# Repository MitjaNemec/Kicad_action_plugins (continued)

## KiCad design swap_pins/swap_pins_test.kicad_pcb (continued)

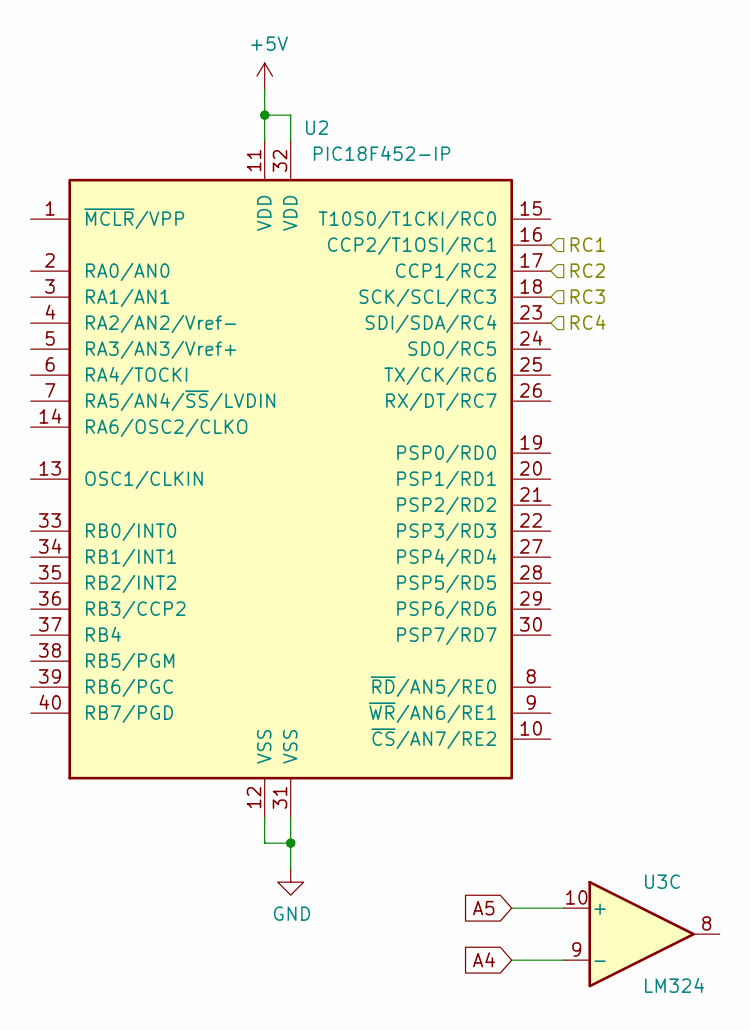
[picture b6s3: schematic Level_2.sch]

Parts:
U1: LM324
U301: PIC18F452-IP; DIP-40_W15.24mm

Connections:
+5V: U301.11 (VDD), U301.32 (VDD); also elsewhere on the board
/level_1/Lavel_2/RC1: U301.16 (CCP2/T1OSI/RC1); also elsewhere on the board
/level_1/Lavel_2/RC2: U301.17 (CCP1/RC2); also elsewhere on the board
/level_1/Lavel_2/RC3: U301.18 (SCK/SCL/RC3); also elsewhere on the board
/level_1/Lavel_2/RC4: U301.23 (SDI/SDA/RC4); also elsewhere on the board
A4: U1.9 (-); also elsewhere on the board
A5: U1.10 (+); also elsewhere on the board
GND: U301.12 (VSS), U301.31 (VSS); also elsewhere on the board

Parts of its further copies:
U2: PIC18F452-IP; DIP-40_W15.24mm

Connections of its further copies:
+5V: U2.11 (VDD), U2.32 (VDD); also elsewhere on the board
/level_1/Level2b/RC1: U2.16 (CCP2/T1OSI/RC1)
/level_1/Level2b/RC2: U2.17 (CCP1/RC2)
/level_1/Level2b/RC3: U2.18 (SCK/SCL/RC3)
/level_1/Level2b/RC4: U2.23 (SDI/SDA/RC4)
GND: U2.12 (VSS), U2.31 (VSS); also elsewhere on the board

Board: 2 copper layers, 24 parts (0 on the bottom side), 23 nets, no tracks yet.

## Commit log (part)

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2018-06-20 Working version
2018-06-20 Add test project file
2018-06-20 changed project to include hierarchical labels also
2018-06-20 Added documentation
2018-06-20 switch to complex plugin type (easier testing)
2018-06-21 Added swap units documentation
2018-06-21 cleanup
2018-06-26 Added instrumentation code to swap_unit
2018-06-27 Fixed an issue when parsing sch files for subsheets
2018-06-27 Minor code formating changes
2018-06-30 Replicate layout: sort replicated sheets.
    Sort sheets to be replicated by the number portion of the reference of
    the pivot module. This means the order is stable (doesn't depend on the
    order the modules are loaded). It also looks better on the PCB as the
    references increment nicely between blocks rather than jumping all over
    the place.
2018-06-30 Replicate layout: copy local module settings.
    The local clearance, solder mask, solder paste margin, solder paste
    margin ratio and zone connection style should be copied to the cloned
    modules.
2018-07-01 Replicate layout: allow text objects to be replicated
    Adds support for replicating standalone text objects (i.e., text not
    associated with a footprint such as a reference). This is a separate
    option in the dialog box (defaults to on) and includes support for
    removing existing text objects from the zones to be cloned.
2018-07-11 Added instrumentation
2018-07-13 Overwritten the plugin with V2 version
2018-08-03 Bugfix to archive-project
    Updated to support spaces in subsheet names. May be OSX specific.
2018-08-17 Updated test files for V5.0
2018-08-17 Changed test project to include complex hierarchy
2018-08-27 adding layout with top level replication done, for bottom level testing
2018-08-28 updated correct test boards
2018-08-29 changed test board for better documentation recording
2018-08-30 Updated documentation of replicate_layout
2018-08-30 Added automatic detection of open Eeschema window
2018-09-11 Fixed a bug in swap_unit plugin to support swapping units where only one unit is placed
2018-09-15 Bugfix: archive_project, handle copy of already archived 3D models gracefully
2018-09-24 Replicate all module text settings
2018-10-09 mode test_project in dedicated folder
2018-10-10 Allow multiple invokations of the archive_project plugin
2018-11-02 Improvements to readme
2018-11-08 Fixed a bug getting the wx.frame due to case of pcbnew application name
    Fixes #22
2018-11-13 Changed the GUI layout for ReplicateLayout
2018-11-23 Additional instrumentation
2018-11-28 Fixed a bug, when a line in .sch file starts with L but is not a part of component description (e.g. Labels, Text, ...)
2018-12-04 Fixed instrumentation
2018-12-20 Allow plugin window to be resized
2019-01-22 managed to keep messagebox focused
2019-01-23 Bugfix: Handle invalid selection of pivot module if selected module is on root level of hierarchy
    Fixes #31
2019-01-31 Gracefully handle common pins swapping Fixed an additional bug
2019-01-31 Fixed another bug in swap_pins
2019-02-02 Add additional layer of error reporting to catch and log errors when trying to run the plugin fails
2019-02-02 minor development enhancement
2019-02-02 Partial fix for complex hierarchy replication. Needs further testing
2019-02-03 Added tests to replicate_layout
2019-02-13 cleaned up the test code
2019-02-13 Added a stub for place_footprints action plugin GUI is more or less in place
2019-02-14 Placement by sheet tested
2019-02-15 Started to update the documentation
2019-02-16 Finalized test code
2019-02-17 Fixed circular placement
2019-02-18 Added forgoten file
2019-02-18 Change GUI a bit in order to enable additional placement options
2019-02-20 Corrected info in copy pasted file header
2019-02-20 Added documentation for net2net action plugin
2019-02-26 upadte info on which versions do net2net and pad2pad work
2019-02-26 update documentation
2019-03-02 Add anchor module reference to the sheet list
2019-03-03 Added calculation of resistance,
2019-03-08 Added length stats plugin with documentation
2019-03-12 updated test suite
2019-03-12 refreshed test suite
2019-03-12 minor change in test code
2019-03-16 updated test project
2019-03-16 Tested archive_project on V5.1
2019-03-17 Added icons
2019-03-19 Split GUI code so that it is completely autogenerated by WxFormBuilder
2019-03-19 Split GUI code
2019-03-19 Tidy up the icons
2019-03-20 Allow selecting tracks, vias or pads
    Fixes #34
2019-03-21 Fixed python3 fix
2019-03-21 Improved error message
2019-03-22 Bugfix (typo)
2019-03-25 Refactor relative local imports to enable back running as a script
2019-03-26 Add flush method to StreamToLogger class for python3 compatibility
    https://github.com/locustio/locust/issues/475
2019-03-26 Added initial instrumentation
2019-03-26 Fix crash when connection between pads has not been found
    Fixes #37
2019-03-27 Python3 compatibility fix
2019-03-27 Added instrumentation, minor styling changes
2019-03-28 First attempt at multiple hierarchy fix. Tested on one project
2019-03-28 instrumentation bugfix
2019-03-28 modified test project
2019-03-29 Fixed handling of multiple hierarchy in swap_pins
2019-04-01 Improved error handling for known errors.
2019-04-02 Allow resize of archive_project GUI
2019-04-02 Fix handling sheet names containing spaces
2019-04-02 Allow resizing of dialog windows
2019-04-09 Added internal version numbers with start commit hook
2019-04-09 SImplified text replication
2019-04-10 Improved errormessages, added error handling
2019-04-11 logging and UI naming cleanup (mostly modules->footprints)
    # Conflicts:
    # copy_layout/copy_layout.py
2019-04-12 Fixed an import bug
2019-04-15 Fixed a bug when swapping units on the same page. Introduced in 8af9e287
2019-04-18 added test suite with reference projects. Reference project have to be checked
2019-04-19 updated test projects
2019-04-19 Added test projects
2019-04-19 Modify test project
2019-04-19 initial architecture in place
2019-04-19 Modified test project. Successfule began importing layout
2019-04-19 saving layout works
2019-04-19 refactor classes
2019-04-19 Applied refactoring, change to saving pickled data
2019-04-19 GUI elements, tested in standalone mode Temporary file handling can be improved
2019-04-19 added forgoten files to test project
2019-04-19 Added icon file
2019-04-19 Added instrumentation and exception handling
2019-04-19 changed test project Added gif animation
2019-04-20 refactor pa2pad to generated GUI code
2019-04-20 Fix bug with swapped models always having wrl ext
    ... regardless of what was actually copied over.
2019-04-24 Added and modified instrumentation
2019-04-24 Updated reference test project
2019-04-24 Added a bit of instrumentation
2019-05-06 added support for any footprint to serve as a reference in linear and circular mode
2019-05-10 Added option to remove nets from the list in lenght_stats
2019-05-11 changed idalog to frame. Does not help
2019-05-12 sort list of netnames
2019-05-12 Sorting by column works
2019-05-16 Solved the highlightning issue
2019-05-21 fixed a bug: forgot to change GUI code in previous commit
2019-05-21 Added logging.shutdown to flush the log
2019-06-18 Additional error checking
2019-06-18 Changed standalone logging added instrumentation
2019-07-15 added plugin icon for lenght_stats
2019-07-27 Added highlight feature to place_footprints
2019-07-28 Added highlight feature to replicate_layout
2019-07-28 updated test project with documentation files
2019-07-28 Solved the GUI issue with documentation checkbox
2019-07-29 swap pcbnew.MODULE.PadsList() as it is removed in newer versions of KiCad for pcbnew.MODULE.Pads()
2019-07-29 Possible fix for V6 compatibility bug
2019-07-30 Swap last couple of calls to *List methods
2019-07-30 cleanup after zone replication refactoring
2019-07-30 Refactor track replication
2019-07-31 Refactored track/via restoration
2019-07-31 Added highlight feature
2019-08-21 Bugfix for matrix layout
    Fixes #61
2019-08-24 Minor UI enhancement
2019-09-04 Archiving worksheet
2019-09-04 Archive both worksheets (PCB ans SCH)
2019-09-06 working progress bar, without threading
2019-09-09 Towards progress report
2019-09-11 Partial fix for issue #64
2019-09-11 Fix the not connected zone replication bug
2019-09-12 Toggle the compatibility hack
2019-09-19 progress bar GUI tested, fixed update of message
2019-10-03 changed the initial position of the dialog
2019-10-07 replicate_layout dialog should now be positioned properly even with multiple screen setup
2019-10-09 correction to Assertion "aNetInfo->GetBoard() == GetBoard()" failed.
2019-10-09 logger.info corrected
2019-10-20 Added option to remove duplicate items (tracks, zones, drawings, text)
2019-11-12 Properly handle nonexistent sheet templates
2019-11-17 Additional instrumentation, proper handling of 3Dmodels with nonexistent path
2019-11-20 Change test project
2019-12-20 Fixed a bug when downloading documentation if it was not a .pdf file
2019-12-29 Bugfix for #74
2020-01-10 Fix syntax error.
    Fixes #76
2020-01-25 Fix case sensitive bug
2020-02-03 Replicate "Keep Upright" as well
    This is necessary for (left,right)-justified text that gets rotated on
    replication. The text will flow in the wrong direction otherwise.
2020-02-16 updated test layouts as the zone filling algorithm changed between 5.1.2 and 5.1.5
2020-02-20 replicate_layout: added option to keep locked footprints in their original position
2020-02-24 Update wxformbuilder->updated generated GUI code
2020-02-24 Removed unused parameter
2020-03-01 Removed unneeded code, changed GUI a bit
2020-03-05 Added os and build version info to log file
2020-03-08 Fixed the 5.1x and 5.99 compatibility
2020-03-08 Removed pcbnew python mocking for 5.1x and 5.99 compatibility. Added intermediate methods to solve this
2020-03-10 Additional fixes for 5.00 getpath compatibility
2020-03-14 Fixed a bug when deleting items when iterating through all items
2020-03-28 change module path compatibility method vith jvpap's approach
2020-03-29 Applied Forty-Bot's bugfix to other instances of get_path
2020-03-30 Gui changes to "source", "destination" nomenclature
2020-04-07 minor documentation corrections
2020-04-11 Add warning for 5.99 users.
2020-06-14 Additional checking for proper schematics and emiting a proper error message
2020-06-14 Place selected footprints only
2020-06-24 Read schematic files as UTF-8
    This allows for UTF-8 in schematic files. As ASCII is also valid UTF-8,
    this is a non-breaking change.
2020-06-25 Added 2.7 compatibility with open file utf-8 support
2020-07-09 fixed a bug when parsing version (introduced when reading files as utf8)
2020-07-22 IndentFixes
2020-08-03 place by selection implemented
2020-12-16 Removed instrumentation
2021-01-07 Better Git Integration
    Added __init__.py so that the plugins can be included in other git projects as a submodule.
2021-01-25 Add sexp_parser
2021-02-03 update README.md with info on 5.99 branch
2021-02-05 Further 5.99 bugfixes
2021-02-19 Updated length_stats/LenghtStats_GUI.fbp Added sorting to the length_stats using the already implemented sort_items function Added button to copy the table to a tab seperated excel ready table to the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
2021-02-23 Fix typo lenght -> length
2021-02-27 Added dots to import statements for python3
2021-03-02 GetFootprintRect -> GetFootprintBoundingBox
2021-03-05 Use wxWindow.GetName() to find the PCB editor window
2021-03-18 Remove parsing of schematics file. Use footprint properties instead.
2021-03-30 solve the end of file bug
2021-06-04 Modified search for wx parent added some debugging code
2021-06-07 Fixed a minor bug
2021-06-30 Improve instructions
2021-08-02 Remove modifying the case in UUID
2021-08-17 avoid the dictionary lookup for the sheet with no footprints
    The sheets without any footprints (only subsheets are present) are not present in self.dict_of_sheets. In 5.99 varsion the plugin gathers schematics info via fooprint.GetProperties methods (Sheetfile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
    Fixes #139
2021-08-17 Add the option to replicate edge cuts items only when required
    Fixes: #117
2021-08-17 Bump version file
